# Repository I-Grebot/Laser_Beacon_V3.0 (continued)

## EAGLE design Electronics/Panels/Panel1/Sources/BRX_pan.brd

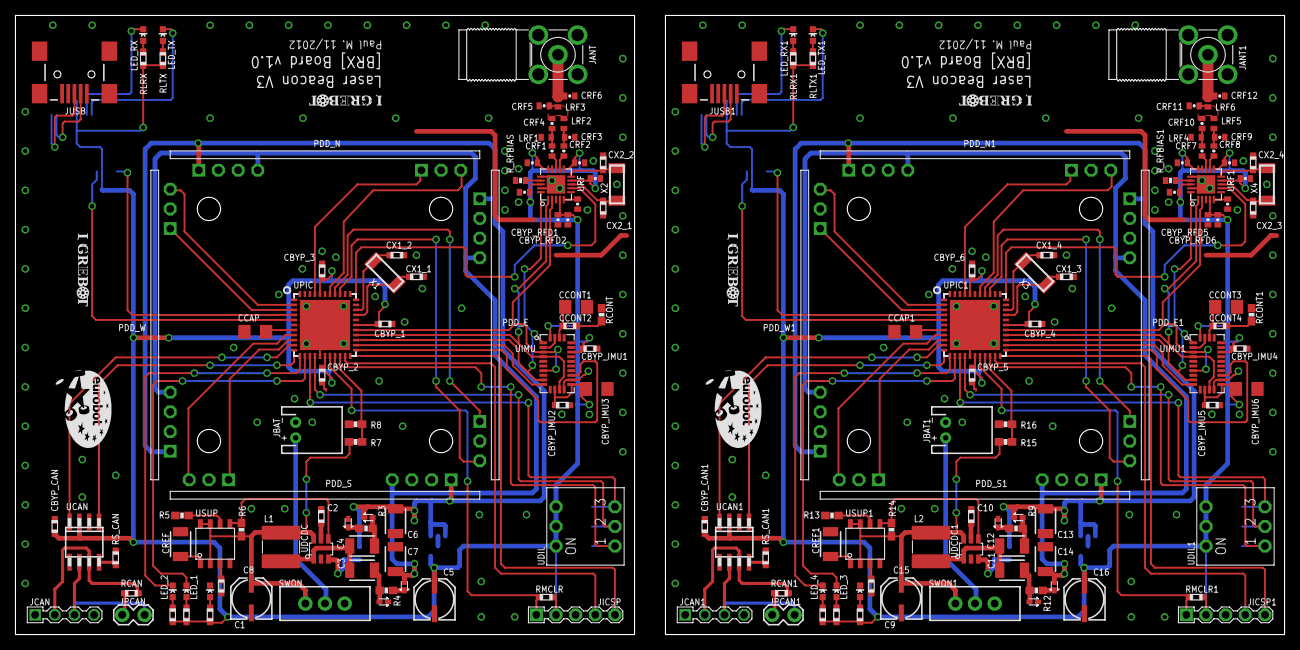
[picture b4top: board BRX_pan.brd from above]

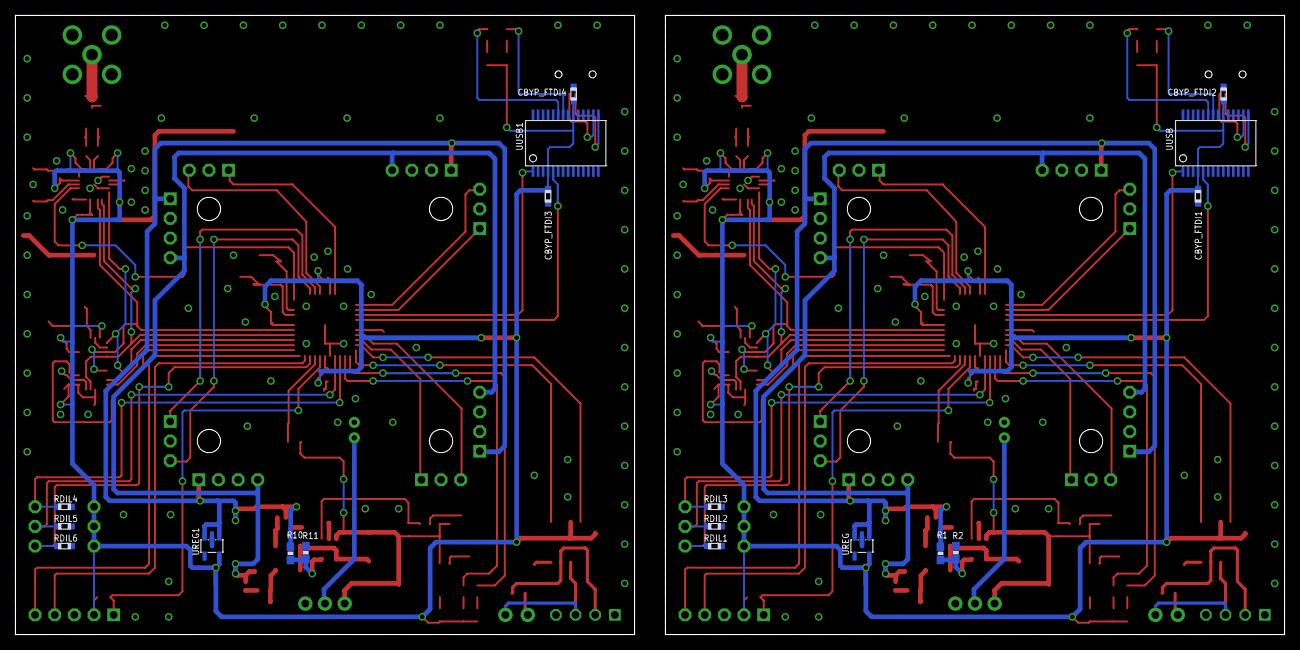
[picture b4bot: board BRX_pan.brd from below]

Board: 2 copper layers, 164.0 x 80.0 mm, 194 parts (18 on the bottom side), 144 nets.

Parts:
C1, C9: 4.7uF; PANASONIC_C
C2, C10: 47nF_16V; R0603
C3, C4, C11, C12: 1uF_16V; 1210
C5, C16: 10uF; PANASONIC_C
C6, C7, C13, C14: 2.2uF_16V; 1210
C8, C15: 470nF; R0603
CBYP_1, CBYP_2, CBYP_3, CBYP_4, CBYP_5, CBYP_6: 100nF_6.3V; R0603
CBYP_CAN, CBYP_CAN1: 100nF_6.3V; R0603
CBYP_FTDI1, CBYP_FTDI2, CBYP_FTDI3, CBYP_FTDI4: 100nF_6.3V; R0603
CBYP_IMU1, CBYP_IMU2, CBYP_IMU4, CBYP_IMU5: 100nF_6.3V; R0603
CBYP_IMU3, CBYP_IMU6: 10uF_6.3V; 1206
CBYP_RFA1, CBYP_RFA2, CBYP_RFA5, CBYP_RFA6: 100nF_X5R; 0402-CAP
CBYP_RFA3, CBYP_RFA4, CBYP_RFA7, CBYP_RFA8: 220pF_X7R; 0402-CAP
CBYP_RFD1, CBYP_RFD3, CBYP_RFD4, CBYP_RFD5: 100nF_X5R; 0402-CAP
CBYP_RFD2, CBYP_RFD6: 220pF_X7R; 0402-CAP
CCAP, CCAP1: 10uF_6.3V; 1206
CCONT1, CCONT3: 10nF; 1206
CCONT2, CCONT4: 470nF; R0603
CREF, CREF1: 1uF; 1210
CRF1, CRF2, CRF7, CRF8: 100pF_NP0; 0402-CAP
CRF3, CRF4, CRF9, CRF10: 1.0pF_NP0; 0402-CAP
CRF5, CRF11: 1.8pF_NP0; 0402-CAP
CRF6, CRF12: 1.5pF_NP0; 0402-CAP
CX1_1, CX1_2, CX1_3, CX1_4, CX2_1, CX2_2, CX2_3, CX2_4: 22pF_6.3V; R0603
D1, D2, D3, D4, D5, D6, D7, D8: PMEG2005; SOD-523
JANT, JANT1: ENG_CD_1814400_C1; SMA-PCB-ANGLE
JBAT, JBAT1: JST-2-PTH
JCAN, JCAN1: SIL4; CON4-2.54
JICSP, JICSP1: SIL5; CON5-2.54
JPCAN, JPCAN1: 1X02_LOCK
JUSB, JUSB1: USBSMD; USB-MINIB
L1, L2: 10uH; L-5X5
LED_1, LED_2, LED_3, LED_4: LED-0603
LED_POW, LED_POW1: LED-0603
LED_RX, LED_RX1: LED-0603
LED_TX, LED_TX1: LED-0603
LRF1, LRF2, LRF3, LRF4, LRF5, LRF6: 1.2nH; C0402
PDD_E, PDD_E1: PDD_BOARD; PDD_SOCKET
PDD_N, PDD_N1: PDD_BOARD; PDD_SOCKET
PDD_S, PDD_S1: PDD_BOARD; PDD_SOCKET
PDD_W, PDD_W1: PDD_BOARD; PDD_SOCKET
R1, R10: 113k; 0603-RES
R2, R11: 13.3k; 0603-RES
R3, R4, R9, R12: 1; 0603-RES
R5, R6, R8, R13, R14, R16: 10k; 0603-RES
R7, R15: 20k; 0603-RES
RCAN, RCAN1: 100; R0603
RCONT, RCONT1: 10k; 0603-RES
RDIL1, RDIL2, RDIL3, RDIL4, RDIL5, RDIL6: 10k; R0603
RL1, RL2, RL3, RL4: 270; R0603
RLPOW, RLPOW1: 270; R0603
RLRX, RLRX1: 270; R0603
RLTX, RLTX1: 270; R0603
RMCLR, RMCLR1: 4.7k; R0603
RS_CAN, RS_CAN1: 10k; R0603
R_RFBIAS, R_RFBIAS1: 56k; 0402-RES
SWON, SWON1: SWITCH-SPDT
U$1, U$4, U$5, U$9: LOGOIGREBOT; LOGO_IGREBOT
U$2, U$3: LOGOEUROBOT; LOGO_EUROBOT_1
UCAN, UCAN1: MCP2551; SO-08
UDCDC, UDCDC1: LT3467A; TSOT-23
UDIL, UDIL1: A6E-3104; SW_DIP-3
UIMU, UIMU1: LSM330DL; LLGA-28
UPIC, UPIC1: DSPIC33FJ128MC804_QFN; QFN44-8X8
UREG, UREG1: MCP1801; SOT23-5L
URF, URF1: CC2500; QFN20-0.5
USUP, USUP1: TL7709AC; SOIC8
UUSB, UUSB1: FT232RL-BASICSSOP; SSOP28DB
X1, X3: 8MHz; XTAL_4.9-1.8
X2, X4: 26MHz; XTAL_4.9-1.8

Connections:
3.3V: C5.+, CBYP_1.1, CBYP_2.1, CBYP_3.1, CBYP_CAN.1, CBYP_FTDI1.1, CBYP_FTDI2.1, CBYP_IMU1.1, CBYP_IMU2.1, CBYP_IMU3.1, CBYP_RFA1.2, CBYP_RFA2.2, CBYP_RFA3.2, CBYP_RFA4.2, CBYP_RFD1.2, CBYP_RFD2.2, JICSP.2, RL1.1, RL2.1, RLPOW.1, RLRX.1, RLTX.1, RMCLR.1, UCAN.3, UDIL.1A, UDIL.2A, UDIL.3A, UIMU.12, UIMU.15, UIMU.22, UIMU.28, UPIC.P$17, UPIC.P$28, UPIC.P$40, UREG.5, URF.4, URF.9, URF.11, URF.14, URF.15, URF.18, UUSB.4, UUSB.20
3.3V1: C16.+, CBYP_4.1, CBYP_5.1, CBYP_6.1, CBYP_CAN1.1, CBYP_FTDI3.1, CBYP_FTDI4.1, CBYP_IMU4.1, CBYP_IMU5.1, CBYP_IMU6.1, CBYP_RFA5.2, CBYP_RFA6.2, CBYP_RFA7.2, CBYP_RFA8.2, CBYP_RFD5.2, CBYP_RFD6.2, JICSP1.2, RL3.1, RL4.1, RLPOW1.1, RLRX1.1, RLTX1.1, RMCLR1.1, UCAN1.3, UDIL1.1A, UDIL1.2A, UDIL1.3A, UIMU1.12, UIMU1.15, UIMU1.22, UIMU1.28, UPIC1.P$17, UPIC1.P$28, UPIC1.P$40, UREG1.5, URF1.4, URF1.9, URF1.11, URF1.14, URF1.15, URF1.18, UUSB1.4, UUSB1.20
!CSN!_A: UIMU.17, UPIC.P$23
!CSN!_A1: UIMU1.17, UPIC1.P$23
!CSN!_G: UIMU.10, UPIC.P$24
!CSN!_G1: UIMU1.10, UPIC1.P$24
!CSN!_RF: UPIC.P$33, URF.7
!CSN!_RF1: UPIC1.P$33, URF1.7
!MCLR!: JICSP.1, RMCLR.2, UPIC.P$18
!MCLR!1: JICSP1.1, RMCLR1.2, UPIC1.P$18
!SHDN!: R6.2, UDCDC.4, USUP.5
!SHDN!1: R14.2, UDCDC1.4, USUP1.5
+12V: C6.1, D1.C, PDD_E.1, PDD_N.1, PDD_S.1, PDD_W.1, R1.2, UREG.1, UREG.3
+12V1: C13.1, D5.C, PDD_E1.1, PDD_N1.1, PDD_S1.1, PDD_W1.1, R10.2, UREG1.1, UREG1.3
-12V: C7.1, D4.A, PDD_E.4, PDD_N.4, PDD_S.4, PDD_W.4
-12V1: C14.1, D8.A, PDD_E1.4, PDD_N1.4, PDD_S1.4, PDD_W1.4
CANH: JCAN.2, RCAN.1, UCAN.7
CANH1: JCAN1.2, RCAN1.1, UCAN1.7
CANL: JCAN.3, JPCAN.2, UCAN.6
CANL1: JCAN1.3, JPCAN1.2, UCAN1.6
CAN_RX: UCAN.4, UPIC.P$10
CAN_RX1: UCAN1.4, UPIC1.P$10
CAN_TX: UCAN.1, UPIC.P$11
CAN_TX1: UCAN1.1, UPIC1.P$11
DIL1: RDIL1.1, UDIL.1B, UPIC.P$20
DIL2: RDIL2.1, UDIL.2B, UPIC.P$15
DIL3: RDIL3.1, UDIL.3B, UPIC.P$14
DIL4: RDIL4.1, UDIL1.3B, UPIC1.P$14
DIL5: RDIL5.1, UDIL1.2B, UPIC1.P$15
DIL6: RDIL6.1, UDIL1.1B, UPIC1.P$20
E_!A-B!: PDD_E.5, UPIC.P$37
E_!A-B!1: PDD_E1.5, UPIC1.P$37
E_!B-A!: PDD_E.7, UPIC.P$36
E_!B-A!1: PDD_E1.7, UPIC1.P$36
GND: C1.-, C2.2, C5.-, C6.2, C7.2, C8.2, CBYP_1.2, CBYP_2.2, CBYP_3.2, CBYP_CAN.2, CBYP_FTDI1.2, CBYP_FTDI2.2, CBYP_IMU1.2, CBYP_IMU2.2, CBYP_IMU3.2, CBYP_RFA1.1, CBYP_RFA2.1, CBYP_RFA3.1, CBYP_RFA4.1, CBYP_RFD1.1, CBYP_RFD2.1, CBYP_RFD3.1, CCAP.2, CCONT1.2, CREF.1, CRF3.1, CRF5.1, CRF6.1, CX1_1.2, CX1_2.2, CX2_1.2, CX2_2.2, D2.A, D3.C, JANT.B1, JANT.B2, JANT.B3, JANT.B4, JBAT.1, JCAN.1, JCAN.4, JICSP.3, JUSB.GND, LED_POW.C, LRF1.1, PDD_E.2, PDD_E.3, PDD_E.6, PDD_N.2, PDD_N.3, PDD_N.6, PDD_S.2, PDD_S.3, PDD_S.6, PDD_W.2, PDD_W.3, PDD_W.6, R2.1, R5.1, R8.1, RCONT.1, RDIL1.2, RDIL2.2, RDIL3.2, RS_CAN.1, R_RFBIAS.2, UCAN.2, UDCDC.2, UIMU.2, UIMU.11, UIMU.14, UIMU.16, UIMU.18, UIMU.19, UIMU.20, UIMU.23, UIMU.24, UIMU.25, UIMU.27, UPIC.P$6, UPIC.P$16, UPIC.P$29, UPIC.P$39, UPIC.PAD, UREG.2, URF.16, URF.19, URF.PAD, USUP.4, UUSB.7, UUSB.18, UUSB.21, UUSB.25, UUSB.26
GND1: C9.-, C10.2, C13.2, C14.2, C15.2, C16.-, CBYP_4.2, CBYP_5.2, CBYP_6.2, CBYP_CAN1.2, CBYP_FTDI3.2, CBYP_FTDI4.2, CBYP_IMU4.2, CBYP_IMU5.2, CBYP_IMU6.2, CBYP_RFA5.1, CBYP_RFA6.1, CBYP_RFA7.1, CBYP_RFA8.1, CBYP_RFD4.1, CBYP_RFD5.1, CBYP_RFD6.1, CCAP1.2, CCONT3.2, CREF1.1, CRF9.1, CRF11.1, CRF12.1, CX1_3.2, CX1_4.2, CX2_3.2, CX2_4.2, D6.A, D7.C, JANT1.B1, JANT1.B2, JANT1.B3, JANT1.B4, JBAT1.1, JCAN1.1, JCAN1.4, JICSP1.3, JUSB1.GND, LED_POW1.C, LRF4.1, PDD_E1.2, PDD_E1.3, PDD_E1.6, PDD_N1.2, PDD_N1.3, PDD_N1.6, PDD_S1.2, PDD_S1.3, PDD_S1.6, PDD_W1.2, PDD_W1.3, PDD_W1.6, R11.1, R13.1, R16.1, RCONT1.1, RDIL4.2, RDIL5.2, RDIL6.2, RS_CAN1.1, R_RFBIAS1.2, UCAN1.2, UDCDC1.2, UIMU1.2, UIMU1.11, UIMU1.14, UIMU1.16, UIMU1.18, UIMU1.19, UIMU1.20, UIMU1.23, UIMU1.24, UIMU1.25, UIMU1.27, UPIC1.P$6, UPIC1.P$16, UPIC1.P$29, UPIC1.P$39, UPIC1.PAD, UREG1.2, URF1.16, URF1.19, URF1.PAD, USUP1.4, UUSB1.7, UUSB1.18, UUSB1.21, UUSB1.25, UUSB1.26
LED_1: LED_1.C, UPIC.P$13
LED_2: LED_2.C, UPIC.P$12
LED_3: LED_3.C, UPIC1.P$13
LED_4: LED_4.C, UPIC1.P$12
LED_RX: LED_RX.C, UUSB.22
LED_RX1: LED_RX1.C, UUSB1.22
LED_TX: LED_TX.C, UUSB.23
LED_TX1: LED_TX1.C, UUSB1.23
MISO: UIMU.3, UIMU.7, UPIC.P$27, URF.2
MISO1: UIMU1.3, UIMU1.7, UPIC1.P$27, URF1.2
MOSI: UIMU.1, UIMU.9, UPIC.P$25, URF.20
MOSI1: UIMU1.1, UIMU1.9, UPIC1.P$25, URF1.20
unnamed: CRF1.2, CRF4.2, LRF1.2
unnamed: LED_TX.A, RLTX.2
unnamed: CRF2.2, CRF3.2, LRF2.1
unnamed: CRF4.1, CRF5.2, LRF2.2, LRF3.1
unnamed: RS_CAN.2, UCAN.8
unnamed: JPCAN.1, RCAN.2
unnamed: CRF6.2, JANT.A, LRF3.2
unnamed: LED_RX.A, RLRX.2
unnamed: LED_1.A, RL1.2
unnamed: LED_2.A, RL2.2
unnamed: C2.1, UDCDC.5
unnamed: JBAT.2, SWON.2
unnamed: C3.1, C4.1, L1.2, UDCDC.1
unnamed: C3.2, D3.A, R4.2
unnamed: D2.C, R3.1
unnamed: C4.2, D1.A, R3.2
unnamed: R5.2, USUP.6
unnamed: R1.1, R2.2, UDCDC.3
unnamed: D4.C, R4.1
unnamed: CCONT2.2, RCONT.2
unnamed: LED_POW.A, RLPOW.2
unnamed: RS_CAN1.2, UCAN1.8
unnamed: CRF7.2, CRF10.2, LRF4.2
unnamed: CRF8.2, CRF9.2, LRF5.1
unnamed: CRF10.1, CRF11.2, LRF5.2, LRF6.1
unnamed: CRF12.2, JANT1.A, LRF6.2
unnamed: JPCAN1.1, RCAN1.2
unnamed: LED_TX1.A, RLTX1.2
unnamed: LED_RX1.A, RLRX1.2
unnamed: LED_3.A, RL3.2
unnamed: LED_4.A, RL4.2
unnamed: C11.1, C12.1, L2.2, UDCDC1.1
unnamed: C10.1, UDCDC1.5
unnamed: D6.C, R9.1
unnamed: C12.2, D5.A, R9.2
unnamed: D8.C, R12.1
unnamed: C11.2, D7.A, R12.2
unnamed: R10.1, R11.2, UDCDC1.3
unnamed: R13.2, USUP1.6
unnamed: JBAT1.2, SWON1.2
unnamed: CCONT4.2, RCONT1.2
unnamed: LED_POW1.A, RLPOW1.2
N_!A-B!: PDD_N.5, UPIC.P$41
N_!A-B!1: PDD_N1.5, UPIC1.P$41
N_!B-A!: PDD_N.7, UPIC.P$38
N_!B-A!1: PDD_N1.7, UPIC1.P$38
PGC: JICSP.5, UPIC.P$22
PGC1: JICSP1.5, UPIC1.P$22
PGD: JICSP.4, UPIC.P$21
PGD1: JICSP1.4, UPIC1.P$21
RF_N: CRF1.1, URF.13
RF_N1: CRF7.1, URF1.13
RF_P: CRF2.1, URF.12
RF_P1: CRF8.1, URF1.12
R_RFBIAS: R_RFBIAS.1, URF.17
R_RFBIAS1: R_RFBIAS1.1, URF1.17
SCLK: UIMU.4, UIMU.13, UPIC.P$26, URF.1
SCLK1: UIMU1.4, UIMU1.13, UPIC1.P$26, URF1.1
SENSE_BAT: R7.2, R8.2, UPIC.P$19
SENSE_BAT1: R15.2, R16.2, UPIC1.P$19
S_!A-B!: PDD_S.5, UPIC.P$9
S_!A-B!1: PDD_S1.5, UPIC1.P$9
S_!B-A!: PDD_S.7, UPIC.P$8
S_!B-A!1: PDD_S1.7, UPIC1.P$8
USBDM: JUSB.D-, UUSB.16
USBDM1: JUSB1.D-, UUSB1.16
USBDP: JUSB.D+, UUSB.15
USBDP1: JUSB1.D+, UUSB1.15
USB_RX: UPIC.P$5, UUSB.5
USB_RX1: UPIC1.P$5, UUSB1.5
USB_TX: UPIC.P$4, UUSB.1
USB_TX1: UPIC1.P$4, UUSB1.1
VBAT: C1.+, L1.1, R6.1, R7.1, SWON.1, UDCDC.6, USUP.2, USUP.7, USUP.8
VBAT1: C9.+, L2.1, R14.1, R15.1, SWON1.1, UDCDC1.6, USUP1.2, USUP1.7, USUP1.8
VCAP: CCAP.1, UPIC.P$7
VCAP1: CCAP1.1, UPIC1.P$7
VCONT: CCONT1.1, CCONT2.1, UIMU.26
VCONT1: CCONT3.1, CCONT4.1, UIMU1.26
VCT: C8.1, USUP.3
VCT1: C15.1, USUP1.3
VDCOUPL: CBYP_RFD3.2, URF.5
VDCOUPL1: CBYP_RFD4.2, URF1.5
VREF: CREF.2, USUP.1
VREF1: CREF1.2, USUP1.1
W_!A-B!: PDD_W.5, UPIC.P$3
W_!A-B!1: PDD_W1.5, UPIC1.P$3
W_!B-A!: PDD_W.7, UPIC.P$2
W_!B-A!1: PDD_W1.7, UPIC1.P$2
X1_OSC1: CX1_1.1, UPIC.P$30, X1.P$1
X1_OSC2: CX1_2.1, UPIC.P$31, X1.P$2
X1_OSC3: CX1_3.1, UPIC1.P$30, X3.P$1
X1_OSC4: CX1_4.1, UPIC1.P$31, X3.P$2
X2_OSC1: CX2_1.1, URF.8, X2.P$1
X2_OSC2: CX2_2.1, URF.10, X2.P$2
X2_OSC3: CX2_3.1, URF1.8, X4.P$1
X2_OSC4: CX2_4.1, URF1.10, X4.P$2

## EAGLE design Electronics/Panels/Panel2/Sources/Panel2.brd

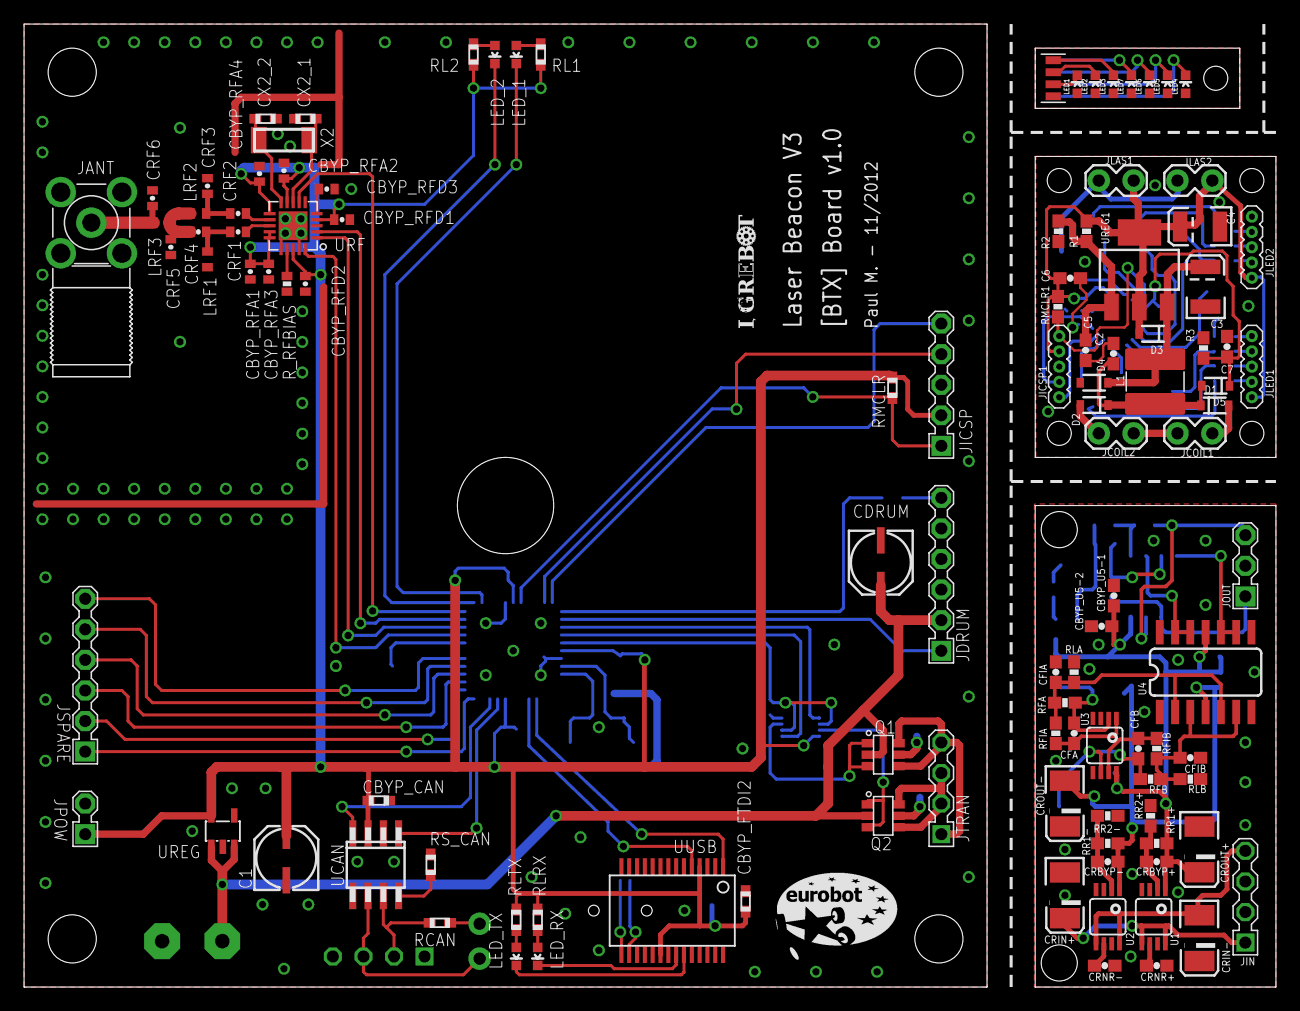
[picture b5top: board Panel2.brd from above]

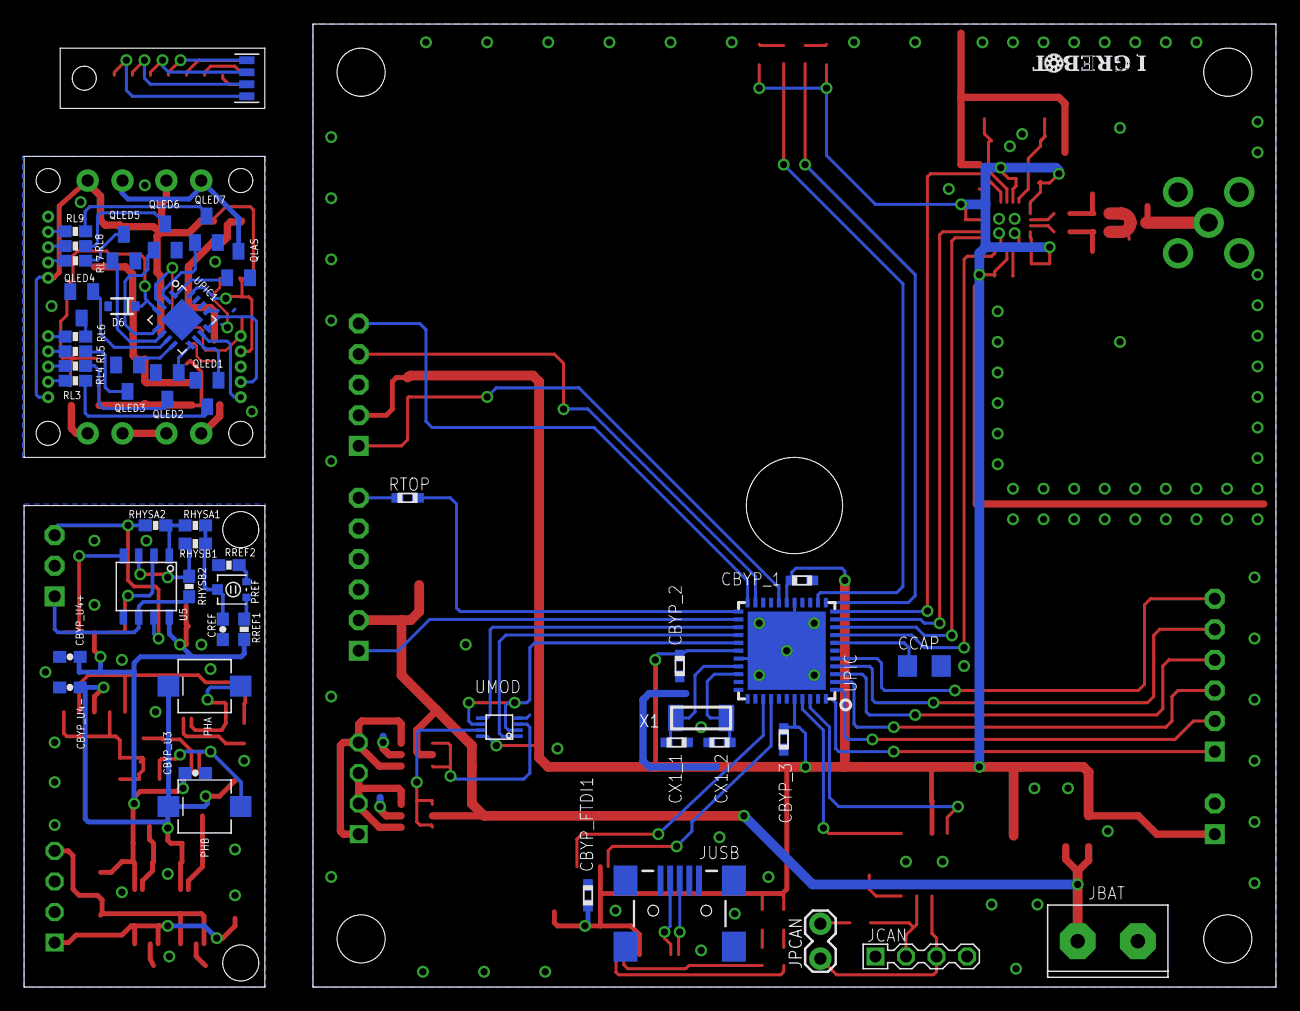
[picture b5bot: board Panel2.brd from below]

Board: 2 copper layers, 104.0 x 80.0 mm, 158 parts (47 on the bottom side), 123 nets.

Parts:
C1: 10uF; PANASONIC_C
C2, C5, C6: 100nF; 0603-CAP
C3, C4: 10uF; EIA3528
C7: 1nF; 0603-CAP
CBYP_1, CBYP_2, CBYP_3: 100nF_6.3V; R0603
CBYP_CAN: 100nF_6.3V; R0603
CBYP_FTDI1, CBYP_FTDI2: 100nF_6.3V; R0603
CBYP_RFA1, CBYP_RFA2: 100nF_X5R; 0402-CAP
CBYP_RFA3, CBYP_RFA4: 220pF_X7R; 0402-CAP
CBYP_RFD1, CBYP_RFD3: 100nF_X5R; 0402-CAP
CBYP_RFD2: 220pF_X7R; 0402-CAP
CBYP_U3, CBYP_U4+, CBYP_U4-, CBYP_U5-1: 1uF; 0603-CAP
CBYP_U5-2: 100nF; 0603-CAP
CCAP: 10uF_6.3V; 1206
CDRUM: 10uF; PANASONIC_C
CFA: 33pF; 0603-CAP
CFB: 33pF; 0603-CAP
CFIA: 100nF; 0603-CAP
CFIB: 100nF; 0603-CAP
CRBYP+: 10nF; 0603-CAP
CRBYP-: 10nF; 0603-CAP
CREF: 470nF; 0603-CAP
CRF1, CRF2: 100pF_NP0; 0402-CAP
CRF3, CRF4: 1.0pF_NP0; 0402-CAP
CRF5: 1.8pF_NP0; 0402-CAP
CRF6: 1.5pF_NP0; 0402-CAP
CRIN+: 10uF; EIA3528-KIT
CRIN-: 10uF; EIA3528-KIT
CRNR+: 10nF; 0603-CAP
CRNR-: 10nF; 0603-CAP
CROUT+: 10uF; EIA3528-KIT
CROUT-: 10uF; EIA3528-KIT
CX1_1, CX1_2, CX2_1, CX2_2: 22pF_6.3V; R0603
D1, D2: PMEG4005AEA; SOD-323
D3: 1N4002; SOD-323
D4, D5: PDZ15B-115; SOD-323
D6: SOD-323
JANT: ENG_CD_1814400_C1; SMA-PCB-ANGLE
JBAT: MULTICOMP_PA001-2; CON2-5.00
JCAN: SIL4; CON4-2.54
JCOIL1, JCOIL2: 1X02_LOCK
JDRUM: SIL6; CON6-2.54
JICSP: SIL5; CON5-2.54
JICSP1: 1X05-1.27MM
JIN: SIL4; CON4-2.54
JLAS1, JLAS2: 1X02_LOCK
JLED: CON8_SMD-1; CON8-SMD-1
JLED1, JLED2: 1X05-1.27MM
JOUT: SIL3; CON3-2.54
JPCAN: 1X02_LOCK
JPOW: SIL2; CON2-2.54
JSPARE: SIL6; CON6-2.54
JTRAN: SIL4; CON4-2.54
JUSB: USBSMD; USB-MINIB
L1: 220uF; L-5X5
LED1, LED2, LED3, LED4, LED5, LED6, LED7: LED-0603
LED_1, LED_2: LED-0603
LED_RX: LED-0603
LED_TX: LED-0603
LRF1, LRF2, LRF3: 1.2nH; C0402
PHA: VBPW34SR
PHB: VBPW34SR
PREF: 100k; TRIM-PVZ2A
Q1, Q2: FDC6333C; SSOT6
QLAS: BSS138; SOT23
QLED1, QLED2, QLED3, QLED4, QLED5, QLED6, QLED7: BSS138; SOT23
R1, R3: 10k; 0603-RES
R2: 14k; 0603-RES
RCAN: 100; R0603
RFA: 20k; 0603-RES
RFB: 20k; 0603-RES
RFIA: 100; 0603-RES
RFIB: 100; 0603-RES
RHYSA1: 100; 0603-RES
RHYSA2: 10k; 0603-RES
RHYSB1: 100; 0603-RES
RHYSB2: 10k; 0603-RES
RL1, RL2: 270; R0603
RL3, RL4, RL5, RL6, RL7, RL8, RL9: 270; 0603-RES
RLA: 100k; 0603-RES
RLB: 100k; 0603-RES
RLRX: 270; R0603
RLTX: 270; R0603
RMCLR: 4.7k; R0603
RMCLR1: 4.7k; 0603-RES
RR1+, RR1-: 31.6k; 0603-RES
RR2+, RR2-: 10k; 0603-RES
RREF1, RREF2: 100; 0603-RES
RS_CAN: 10k; R0603
RTOP: 100; R0603
R_RFBIAS: 56k; 0402-RES
U1: TPS7A4901NO_PAD; MSOP8
U2: TPS7A3001NO_PAD; MSOP8
U3: OPA2380; MSOP8
U4: INA2143; SOIC14
U5: TLV3502; SOIC8
U$3: LOGOEUROBOT; LOGO_EUROBOT_1
U$5, U$9: LOGOIGREBOT; LOGO_IGREBOT
UCAN: MCP2551; SO-08
UMOD: SN74LVC2G08DCU; DCU8
UPIC: DSPIC33FJ128MC804_QFN; QFN44-8X8
UPIC1: PIC16F1825; QFN16-0.65
UREG: MCP1801; SOT23-5L
UREG1: TLV1117; SOT223
URF: CC2500; QFN20-0.5
UUSB: FT232RL-BASICSSOP; SSOP28DB
X1: 8MHz; XTAL_4.9-1.8
X2: 26MHz; XTAL_4.9-1.8

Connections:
3.3V: C1.+, CBYP_1.1, CBYP_2.1, CBYP_3.1, CBYP_CAN.1, CBYP_FTDI1.1, CBYP_FTDI2.1, CBYP_RFA1.2, CBYP_RFA2.2, CBYP_RFA3.2, CBYP_RFA4.2, CBYP_RFD1.2, CBYP_RFD2.2, JICSP.2, JPOW.1, RL1.1, RL2.1, RLRX.1, RLTX.1, RMCLR.1, UCAN.3, UMOD.8, UPIC.P$17, UPIC.P$28, UPIC.P$40, UREG.5, URF.4, URF.9, URF.11, URF.14, URF.15, URF.18, UUSB.4, UUSB.20
!CMP_A-B!: JOUT.1, RHYSB2.2, U5.6
!CMP_B-A!: JOUT.3, RHYSA2.2, U5.7
!MCLR!: JICSP.1, RMCLR.2, UPIC.P$18
!MCLR!1: JICSP1.1, RMCLR1.1, UPIC1.3
+3V3: C4.A, C6.1, D3.2, JICSP1.2, JLAS1.1, JLAS2.1, JLED1.1, JLED2.1, R1.2, RMCLR1.2, UPIC1.16, UREG1.2, UREG1.4
+5V: CBYP_U3.1, CBYP_U4+.1, CBYP_U5-1.1, CBYP_U5-2.1, CRBYP+.1, CROUT+.A, RR1+.2, RREF1.1, U1.1, U3.8, U4.11, U5.8
+12V: CDRUM.+, JBAT.1, JDRUM.2, Q1.2, Q2.2, UREG.1, UREG.3
-5V: CBYP_U4-.2, CRBYP-.1, CROUT-.C, PHA.A, PHB.A, RR1-.2, U2.1, U4.4
AGND: CBYP_U3.2, CBYP_U4+.2, CBYP_U4-.1, CBYP_U5-1.2, CBYP_U5-2.2, CFIA.2, CFIB.2, CREF.2, CRIN+.C, CRIN-.A, CRNR+.2, CRNR-.2, CROUT+.C, CROUT-.A, JIN.2, JIN.3, JOUT.2, RLA.1, RLB.1, RR2+.1, RR2-.1, RREF2.1, U1.4, U2.4, U3.3, U3.4, U3.5, U4.8, U4.14, U5.5
CANH: JCAN.2, RCAN.1, UCAN.7
CANL: JCAN.3, JPCAN.2, UCAN.6
CAN_RX: UCAN.4, UPIC.P$42
CAN_TX: UCAN.1, UPIC.P$41
DRUM_PWM: JDRUM.1, UPIC.P$24
DRUM_TOP: RTOP.1, UPIC.P$23
GND: C1.-, CBYP_1.2, CBYP_2.2, CBYP_3.2, CBYP_CAN.2, CBYP_FTDI1.2, CBYP_FTDI2.2, CBYP_RFA1.1, CBYP_RFA2.1, CBYP_RFA3.1, CBYP_RFA4.1, CBYP_RFD1.1, CBYP_RFD2.1, CBYP_RFD3.1, CCAP.2, CDRUM.-, CRF3.1, CRF5.1, CRF6.1, CX1_1.2, CX1_2.2, CX2_1.2, CX2_2.2, JANT.B1, JANT.B2, JANT.B3, JANT.B4, JBAT.2, JCAN.1, JCAN.4, JDRUM.3, JDRUM.5, JICSP.3, JPOW.2, JUSB.GND, LRF1.1, Q1.5, Q2.5, RS_CAN.1, R_RFBIAS.2, UCAN.2, UMOD.4, UPIC.P$6, UPIC.P$16, UPIC.P$29, UPIC.P$39, UPIC.PAD, UREG.2, URF.16, URF.19, URF.PAD, UUSB.7, UUSB.18, UUSB.21, UUSB.25, UUSB.26
GND1: C2.2, C3.C, C4.C, C5.2, C6.2, C7.2, D4.2, D6.2, JCOIL1.2, JCOIL2.2, JICSP1.3, JLED2.5, QLAS.2, QLED1.2, QLED2.2, QLED3.2, QLED4.2, QLED5.2, QLED6.2, QLED7.2, R2.1, R3.1, UPIC1.13
LAS_ON: QLAS.1, UPIC1.1
LAS_POW: JLAS1.2, JLAS2.2, QLAS.3
LED_1: LED_1.C, UPIC.P$13
LED_2: LED_2.C, UPIC.P$12
LED_ON1: QLED1.1, UPIC1.10
LED_ON2: QLED2.1, UPIC1.9
LED_ON3: QLED3.1, UPIC1.8
LED_ON4: QLED4.1, UPIC1.7
LED_ON5: QLED5.1, UPIC1.6
LED_ON6: QLED6.1, UPIC1.5
LED_ON7: QLED7.1, UPIC1.2
LED_POW1: JLED1.2, RL3.2
LED_POW2: JLED1.3, RL4.2
LED_POW3: JLED1.4, RL5.2
LED_POW4: JLED1.5, RL6.2
LED_POW5: JLED2.2, RL7.2
LED_POW6: JLED2.3, RL8.2
LED_POW7: JLED2.4, RL9.2
LED_RX: LED_RX.C, UUSB.22
LED_TX: LED_TX.C, UUSB.23
MOD_N: Q1.1, Q1.3, UMOD.3
MOD_P: Q2.1, Q2.3, UMOD.7
MOD_PWM_N: UMOD.5, UPIC.P$25
MOD_PWM_P: UMOD.1, UPIC.P$26
MOD_TX: UMOD.2, UMOD.6, UPIC.P$27
unnamed: CRF1.2, CRF4.2, LRF1.2
unnamed: LED_TX.A, RLTX.2
unnamed: CRF2.2, CRF3.2, LRF2.1
unnamed: CRF4.1, CRF5.2, LRF2.2, LRF3.1
unnamed: RS_CAN.2, UCAN.8
unnamed: JPCAN.1, RCAN.2
unnamed: CRF6.2, JANT.A, LRF3.2
unnamed: LED_RX.A, RLRX.2
unnamed: LED_1.A, RL1.2
unnamed: LED_2.A, RL2.2
unnamed: D1.2, JCOIL1.1
unnamed: D2.2, JCOIL2.1
unnamed: C5.1, R1.1, R2.2, UREG1.1
unnamed: QLED1.3, RL3.1
unnamed: QLED2.3, RL4.1
unnamed: QLED3.3, RL5.1
unnamed: QLED4.3, RL6.1
unnamed: QLED5.3, RL7.1
unnamed: QLED6.3, RL8.1
unnamed: QLED7.3, RL9.1
unnamed: JLED.2, LED1.C
unnamed: JLED.3, LED2.C
unnamed: JLED.4, LED3.C
unnamed: JLED.5, LED4.C
unnamed: JLED.6, LED5.C
unnamed: JLED.7, LED6.C
unnamed: JLED.8, LED7.C
unnamed: JLED.1, LED1.A, LED2.A, LED3.A, LED4.A, LED5.A, LED6.A, LED7.A
unnamed: CRNR+.1, U1.6
unnamed: CRNR-.1, U2.6
unnamed: CRBYP+.2, RR1+.1, RR2+.2, U1.2
unnamed: CRBYP-.2, RR1-.1, RR2-.2, U2.2
unnamed: CFA.2, RFIA.1, U3.1
unnamed: CFA.1, PHA.K, RFA.1, U3.2
unnamed: CFB.2, RFIB.1, U3.7
unnamed: CFB.1, PHB.K, RFB.1, U3.6
unnamed: RHYSA1.2, RHYSA2.1, U5.1
unnamed: RHYSB1.2, RHYSB2.1, U5.3
unnamed: PREF.1, RREF1.2
unnamed: PREF.3, RREF2.2
PGC: JICSP.5, UPIC.P$22
PGC1: JICSP1.5, UPIC1.11
PGD: JICSP.4, UPIC.P$21
PGD1: JICSP1.4, UPIC1.12
RF_!CSN!: UPIC.P$11, URF.7
RF_MISO: UPIC.P$10, URF.2
RF_MOSI: UPIC.P$8, URF.20
RF_N: CRF1.1, URF.13
RF_P: CRF2.1, URF.12
RF_SCLK: UPIC.P$9, URF.1
RTOP: JDRUM.6, RTOP.2
R_RFBIAS: R_RFBIAS.1, URF.17
SPARE1: JSPARE.1, UPIC.P$44
SPARE2: JSPARE.2, UPIC.P$1
SPARE3: JSPARE.3, UPIC.P$2
SPARE4: JSPARE.4, UPIC.P$3
SPARE5: JSPARE.5, UPIC.P$4
SPARE6: JSPARE.6, UPIC.P$5
SUB_A-B: U4.9, U4.10, U5.4
SUB_B-A: U4.12, U4.13, U5.2
TI_A: CFIA.1, RFA.2, RFIA.2, RLA.2, U4.2, U4.5
TI_B: CFIB.1, RFB.2, RFIB.2, RLB.2, U4.3, U4.6
TRANSF_N: JTRAN.2, JTRAN.3, Q2.4, Q2.6
TRANSF_P: JTRAN.1, JTRAN.4, Q1.4, Q1.6
UART_RX: C7.1, D5.1, D6.1, R3.2, UPIC1.4
USBDM: JUSB.D-, UUSB.16
USBDP: JUSB.D+, UUSB.15
USB_RX: UPIC.P$37, UUSB.5
USB_TX: UPIC.P$36, UUSB.1
VCAP: CCAP.1, UPIC.P$7
VDC: C2.1, D1.1, D2.1, D5.2, L1.1
VDCOUPL: CBYP_RFD3.2, URF.5
VIN: C3.A, D3.1, D4.1, L1.2, UREG1.3
VIN+: CRIN+.A, JIN.1, U1.5, U1.8
VIN-: CRIN-.C, JIN.4, U2.5, U2.8
VREF: CREF.1, PREF.2, RHYSA1.1, RHYSB1.1
X1_OSC1: CX1_1.1, UPIC.P$30, X1.P$1
X1_OSC2: CX1_2.1, UPIC.P$31, X1.P$2
X2_OSC1: CX2_1.1, URF.8, X2.P$1
X2_OSC2: CX2_2.1, URF.10, X2.P$2
